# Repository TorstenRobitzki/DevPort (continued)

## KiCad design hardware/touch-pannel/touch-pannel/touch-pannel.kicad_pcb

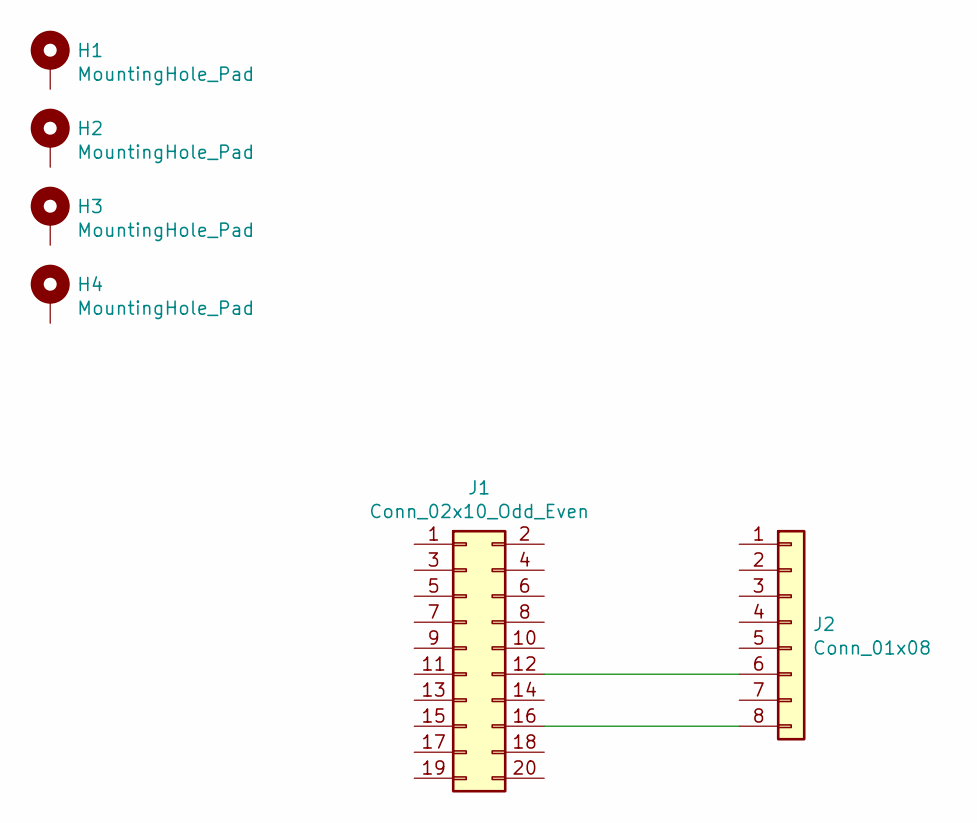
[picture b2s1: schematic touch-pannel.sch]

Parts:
H1, H2, H3, H4: MountingHole_Pad; MountingHole_3.2mm_M3_Pad_Via
J1: Conn_02x10_Odd_Even; Molex_SlimStack_52991-0208_2x10_P0.50mm_Vertical
J2: Conn_01x08; wheel

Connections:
unnamed: H1.1, H1.~
unnamed: J1.2, J2.1
unnamed: J1.4, J2.2
unnamed: J1.6, J2.3
unnamed: J1.8, J2.4
unnamed: J1.10, J2.5
unnamed: J1.12, J2.6
unnamed: J1.14, J2.7
unnamed: J1.16, J2.8

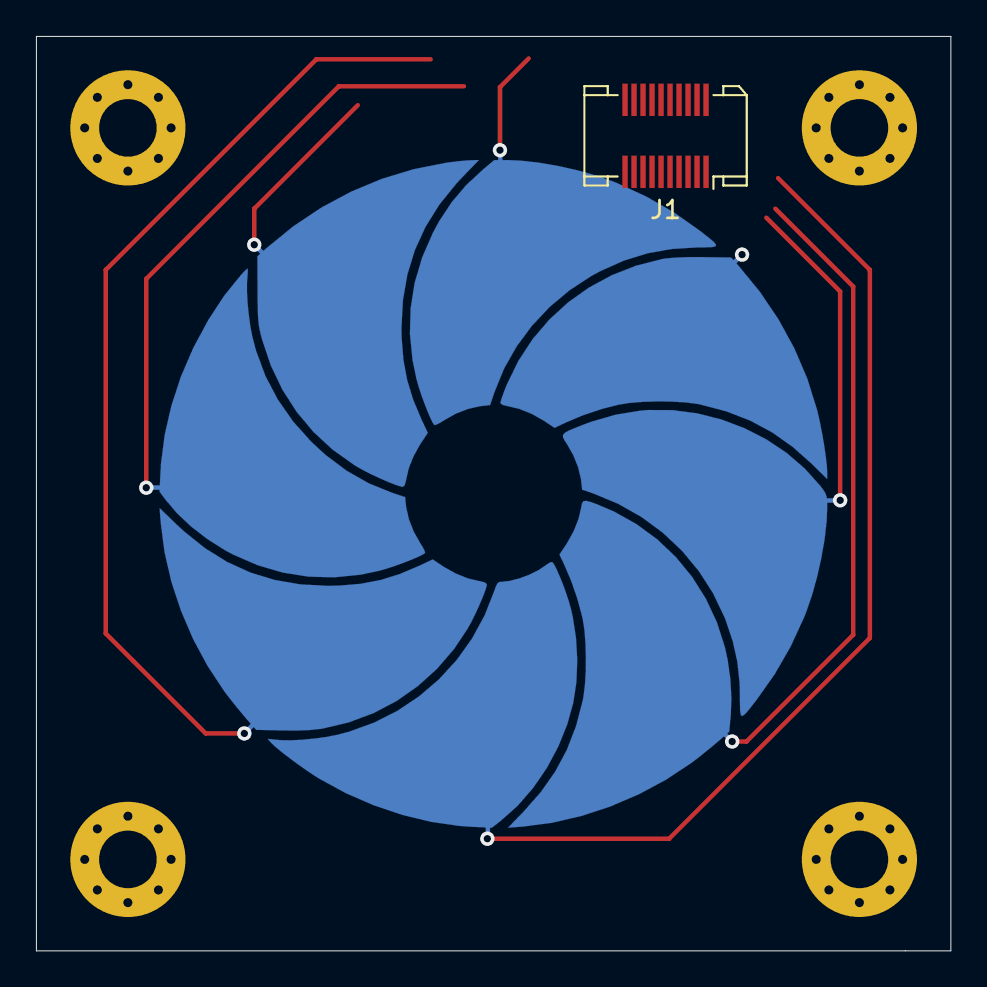
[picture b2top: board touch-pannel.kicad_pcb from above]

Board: 2 copper layers, 50.8 x 50.8 mm, 6 parts (1 on the bottom side), 9 nets.

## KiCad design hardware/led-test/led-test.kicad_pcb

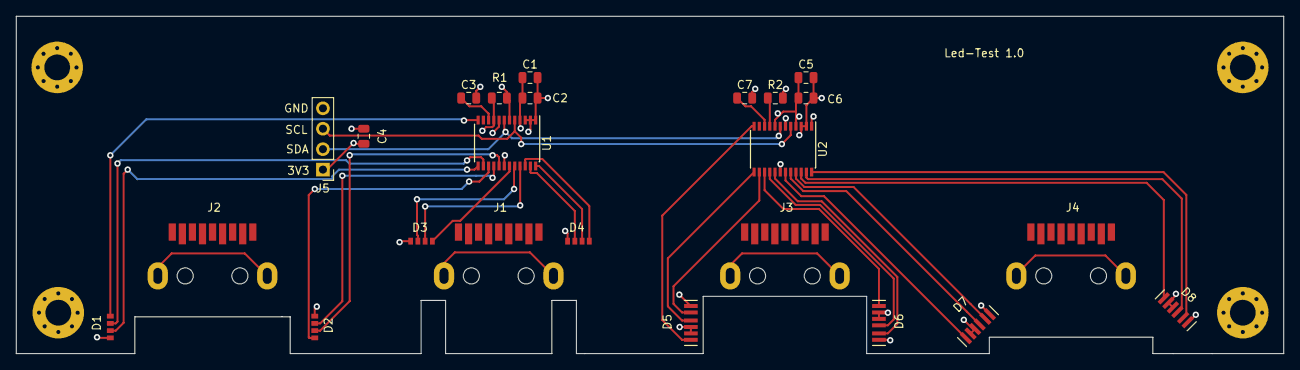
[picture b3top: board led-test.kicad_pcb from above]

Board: 4 copper layers, 157.5 x 41.9 mm, 24 parts (0 on the bottom side), 32 nets.

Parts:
C1, C3, C5, C7: 1µF; C_0805_2012Metric
C2, C6: 0.1µF; C_0805_2012Metric
C4: 10µF; C_0805_2012Metric
D1, D2, D3, D4: LED_AGBR; MSL0601RGB
D5, D6, D7, D8: LED_RGB; KRTB_AELPS1.32
J1, J2, J3, J4: USB3_A; WR-COM_USB_3.0_Horizontal_SMT
J5: Conn_01x04_Male; PinHeader_1x04_P2.54mm_Vertical
R1, R2: 3.6k; R_0805_2012Metric
U1, U2: LP5012PWR; TSSOP-24_4.4x7.8mm_P0.65mm

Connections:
+3V3: C1.1, C2.1, C4.1, C5.1, C6.1, D1.1, D2.1, D3.1, D4.1, D5.4, D5.5, D5.6, D6.4, D6.5, D6.6, D7.4, D7.5, D7.6, D8.4, D8.5, D8.6, J5.1, U1.4, U1.8, U2.1, U2.4, U2.8
/SCL: J5.3, U1.5, U2.5
/SDA: J5.2, U1.7, U2.7
GND: C1.2, C2.2, C3.2, C4.2, C5.2, C6.2, C7.2, J5.4, R1.2, R2.2, U1.1, U1.2, U1.3, U1.6, U1.18, U2.2, U2.3, U2.6, U2.18
unnamed: C3.1, U1.10
unnamed: C7.1, U2.10
unnamed: D1.2, U1.13
unnamed: D1.3, U1.14
unnamed: D1.4, U1.12
unnamed: D2.2, U1.16
unnamed: D2.3, U1.17
unnamed: D2.4, U1.15
unnamed: D3.2, U1.20
unnamed: D3.3, U1.21
unnamed: D3.4, U1.19
unnamed: D4.2, U1.23
unnamed: D4.3, U1.24
unnamed: D4.4, U1.22
unnamed: D5.1, U2.12
unnamed: D5.2, U2.13
unnamed: D5.3, U2.14
unnamed: D6.1, U2.15
unnamed: D6.2, U2.16
unnamed: D6.3, U2.17
unnamed: D7.1, U2.19
unnamed: D7.2, U2.20
unnamed: D7.3, U2.21
unnamed: D8.1, U2.22
unnamed: D8.2, U2.23
unnamed: D8.3, U2.24
unnamed: R1.1, U1.9
unnamed: R2.1, U2.9

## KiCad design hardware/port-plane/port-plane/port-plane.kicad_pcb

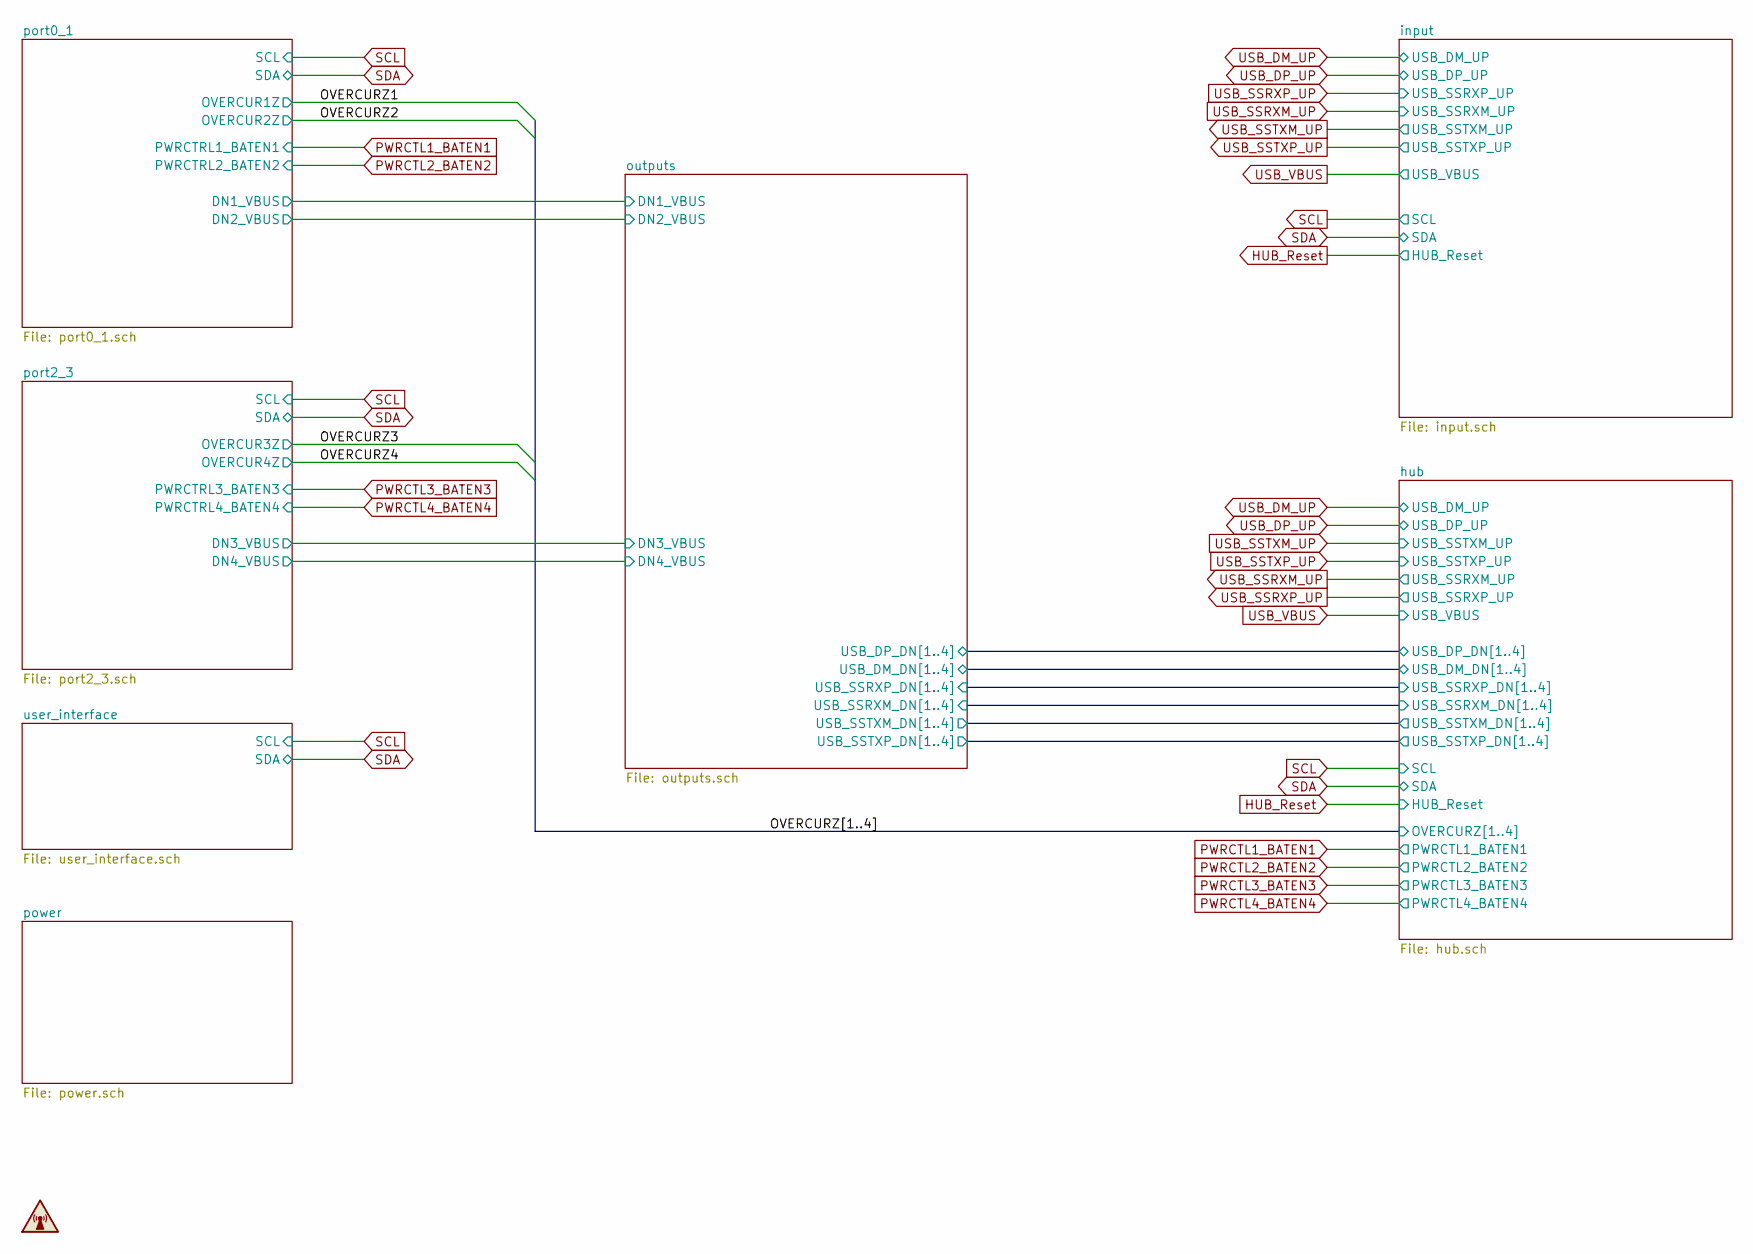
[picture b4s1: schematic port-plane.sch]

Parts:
SYM1: SYM_Radio_Waves_Small; Torrox_Black

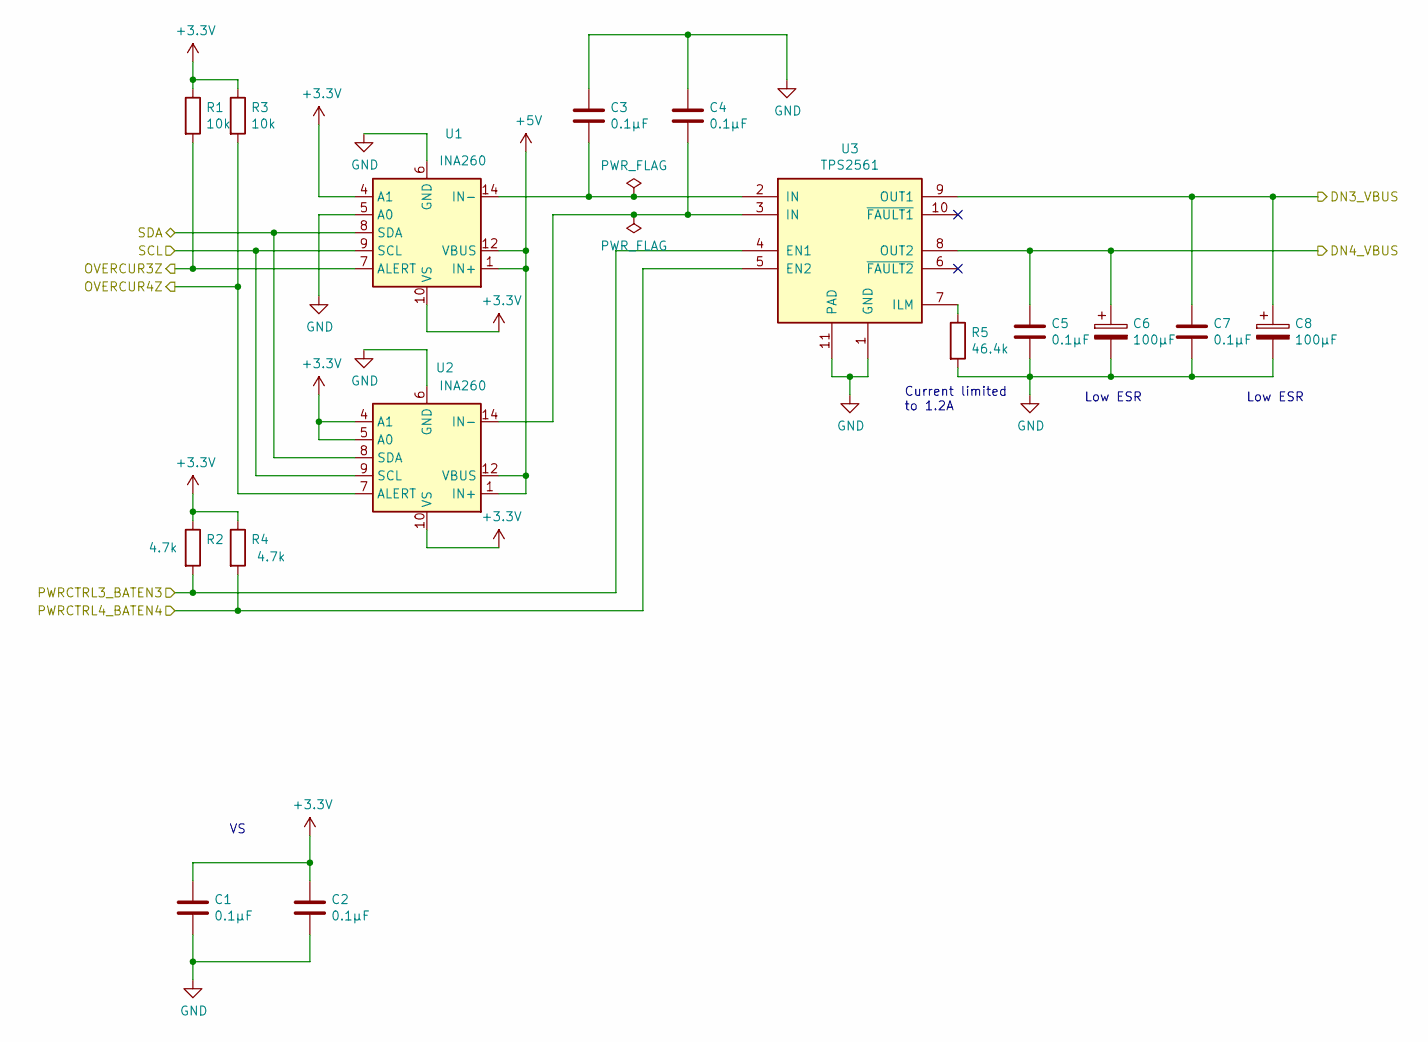
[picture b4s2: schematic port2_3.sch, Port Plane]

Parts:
C1, C2, C3, C4, C5, C7: 0.1µF; C_0603_1608Metric
C6, C8: 100µF; C_Elec_6.3x7.7
R1, R3: 10k; R_0603_1608Metric
R2, R4: 4.7k; R_0603_1608Metric
R5: 46.4k; R_0603_1608Metric
U1, U2: INA260; TSSOP-16_4.4x5mm_P0.65mm
U3: TPS2561; VSON-10-1EP_3x3mm_P0.5mm_EP1.65x2.4mm_ThermalVias

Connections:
+5V: U1.1 (IN+), U1.2 (IN+), U1.3 (IN+), U1.12 (VBUS), U2.1 (IN+), U2.2 (IN+), U2.3 (IN+), U2.12 (VBUS); also elsewhere on the board
/OVERCURZ3: R1.2, U1.7 (ALERT); also elsewhere on the board
/OVERCURZ4: R3.2, U2.7 (ALERT); also elsewhere on the board
/outputs/DN3_VBUS: C7.1, C8.1, U3.9 (OUT1); also elsewhere on the board
/outputs/DN4_VBUS: C5.1, C6.1, U3.8 (OUT2); also elsewhere on the board
GND: C1.2, C2.2, C3.1, C4.1, C5.2, C6.2, C7.2, C8.2, R5.2, U1.5 (A0), U1.6 (GND), U1.11 (GND), U2.6 (GND), U2.11 (GND), U3.1 (GND), U3.11 (PAD); also elsewhere on the board
unnamed: C3.2, U1.14 (IN-), U1.15 (IN-), U1.16 (IN-), U3.2 (IN)
unnamed: C4.2, U2.14 (IN-), U2.15 (IN-), U2.16 (IN-), U3.3 (IN)
unnamed: R5.1, U3.7 (ILM)
PWRCTL3_BATEN3: R2.2, U3.4 (EN1); also elsewhere on the board
PWRCTL4_BATEN4: R4.2, U3.5 (EN2); also elsewhere on the board

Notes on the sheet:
Current limited to 1.2A
Low ESR

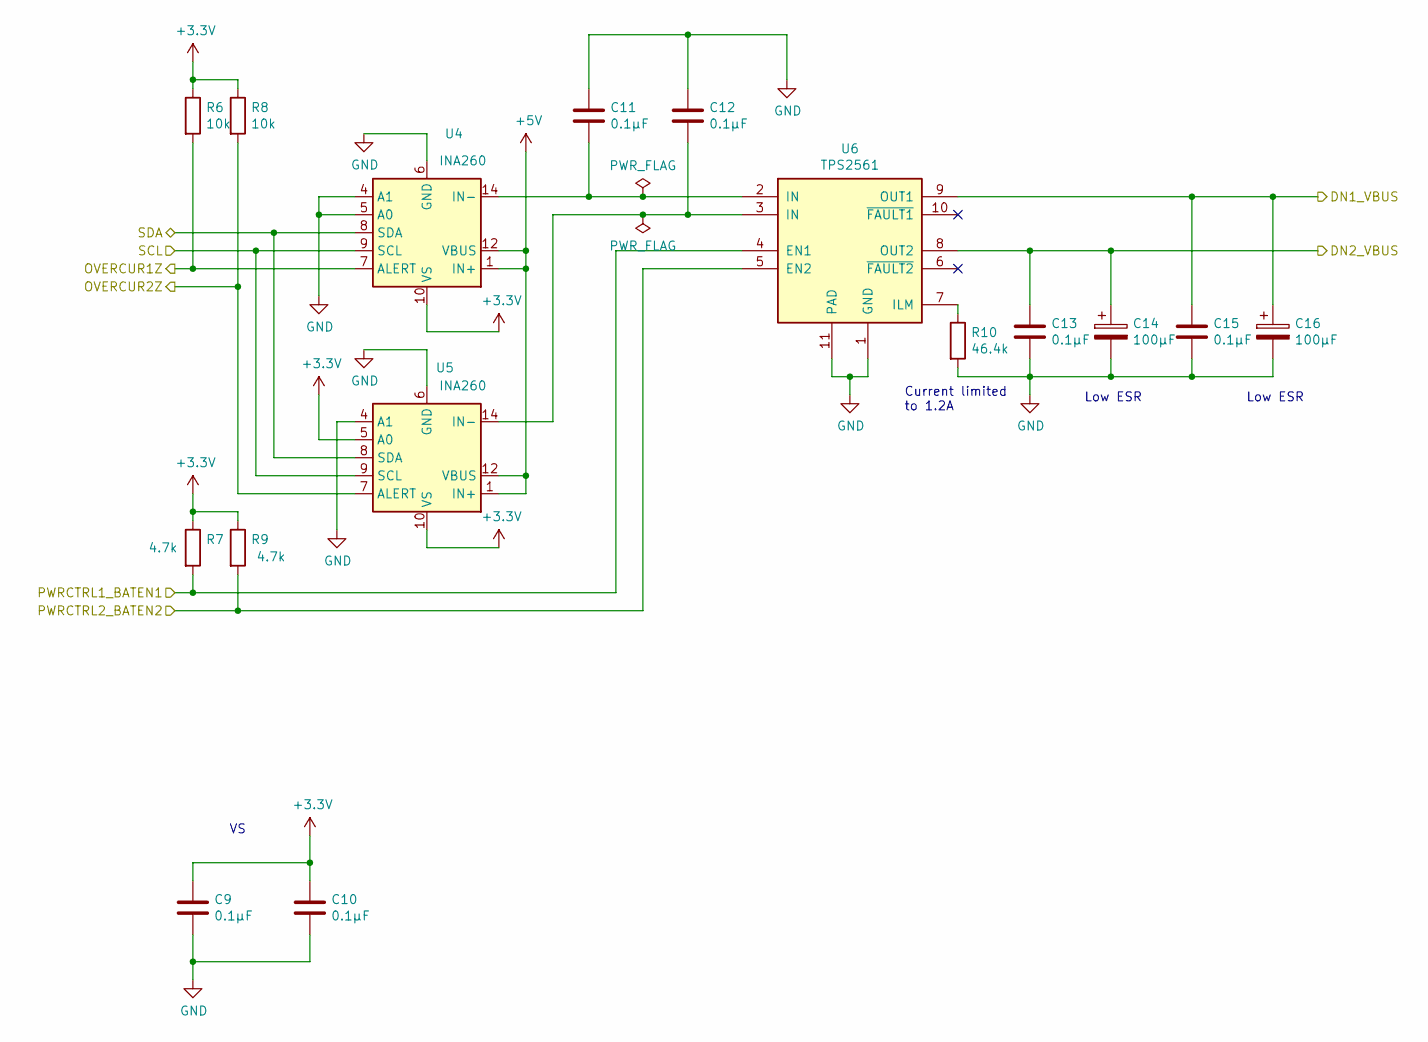
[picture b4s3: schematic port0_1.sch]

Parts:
C9, C10, C11, C12, C13, C15: 0.1µF; C_0603_1608Metric
C14, C16: 100µF; C_Elec_6.3x7.7
R6, R8: 10k; R_0603_1608Metric
R7, R9: 4.7k; R_0603_1608Metric
R10: 46.4k; R_0603_1608Metric
U4, U5: INA260; TSSOP-16_4.4x5mm_P0.65mm
U6: TPS2561; VSON-10-1EP_3x3mm_P0.5mm_EP1.65x2.4mm_ThermalVias

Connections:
+5V: U4.1 (IN+), U4.2 (IN+), U4.3 (IN+), U4.12 (VBUS), U5.1 (IN+), U5.2 (IN+), U5.3 (IN+), U5.12 (VBUS); also elsewhere on the board
/OVERCURZ1: R6.2, U4.7 (ALERT); also elsewhere on the board
/OVERCURZ2: R8.2, U5.7 (ALERT); also elsewhere on the board
/outputs/DN1_VBUS: C15.1, C16.1, U6.9 (OUT1); also elsewhere on the board
/outputs/DN2_VBUS: C13.1, C14.1, U6.8 (OUT2); also elsewhere on the board
GND: C9.2, C10.2, C11.1, C12.1, C13.2, C14.2, C15.2, C16.2, R10.2, U4.4 (A1), U4.5 (A0), U4.6 (GND), U4.11 (GND), U5.4 (A1), U5.6 (GND), U5.11 (GND), U6.1 (GND), U6.11 (PAD); also elsewhere on the board
unnamed: C11.2, U4.14 (IN-), U4.15 (IN-), U4.16 (IN-), U6.2 (IN)
unnamed: C12.2, U5.14 (IN-), U5.15 (IN-), U5.16 (IN-), U6.3 (IN)
unnamed: R10.1, U6.7 (ILM)
PWRCTL1_BATEN1: R7.2, U6.4 (EN1); also elsewhere on the board
PWRCTL2_BATEN2: R9.2, U6.5 (EN2); also elsewhere on the board

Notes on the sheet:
Current limited to 1.2A
Low ESR

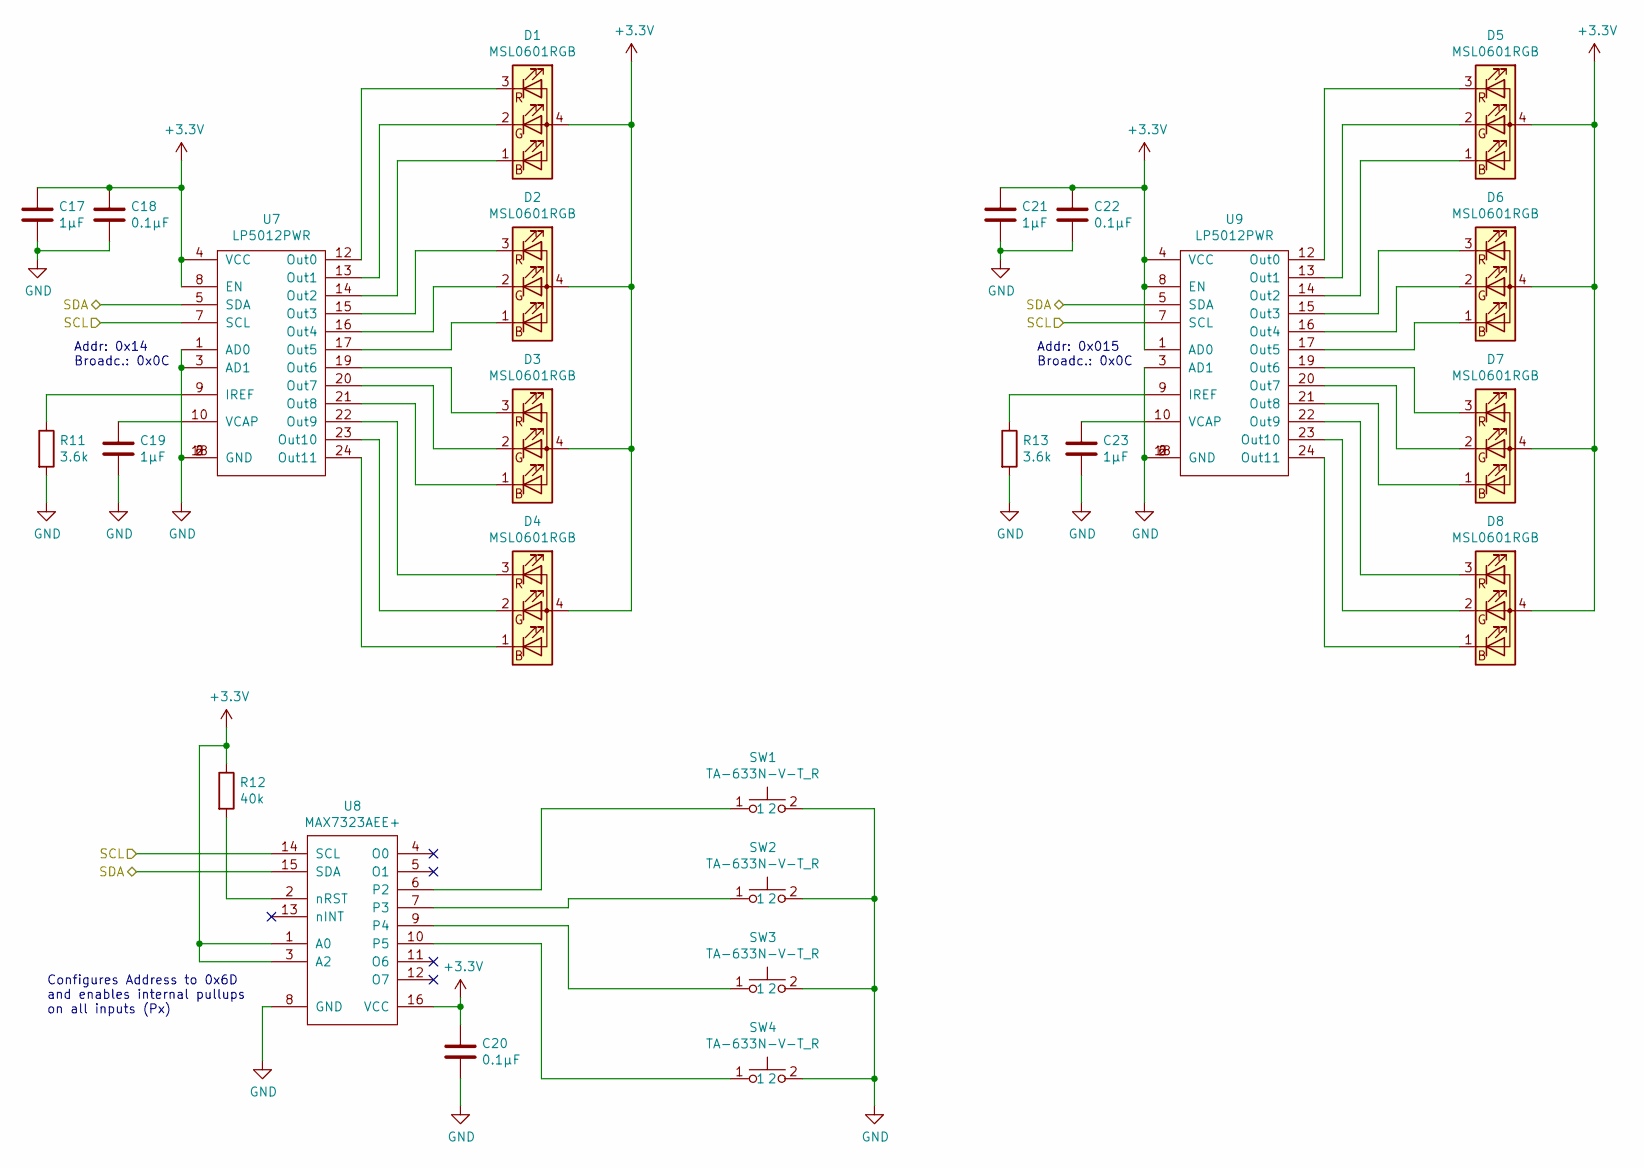
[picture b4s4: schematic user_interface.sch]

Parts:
C17, C19, C21, C23: 1µF; C_0603_1608Metric
C18, C20, C22: 0.1µF; C_0603_1608Metric
D1, D2, D3, D4, D5, D6, D7, D8: MSL0601RGB
R11, R13: 3.6k; R_0603_1608Metric
R12: 40k; R_0603_1608Metric
SW1, SW2, SW3, SW4: TA-633N-V-T_R; TA-633
U7, U9: LP5012PWR; TSSOP-24_4.4x7.8mm_P0.65mm
U8: MAX7323AEE+; TSSOP-24_4.4x7.8mm_P0.65mm

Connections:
GND: C17.2, C18.2, C19.2, C20.2, C21.2, C22.2, C23.2, R11.2, R13.2, SW1.2, SW2.2, SW3.2, SW4.2, U7.1 (AD0), U7.2 (GND), U7.3 (AD1), U7.6 (GND), U7.18 (GND), U8.8 (GND), U9.2 (GND), U9.3 (AD1), U9.6 (GND), U9.18 (GND); also elsewhere on the board
unnamed: C19.1, U7.10 (VCAP)
unnamed: C23.1, U9.10 (VCAP)
unnamed: D1.1 (BK), U7.14 (Out2)
unnamed: D1.2 (GK), U7.13 (Out1)
unnamed: D1.3 (RK), U7.12 (Out0)
unnamed: D2.1 (BK), U7.17 (Out5)
unnamed: D2.2 (GK), U7.16 (Out4)
unnamed: D2.3 (RK), U7.15 (Out3)
unnamed: D3.1 (BK), U7.21 (Out8)
unnamed: D3.2 (GK), U7.20 (Out7)
unnamed: D3.3 (RK), U7.19 (Out6)
unnamed: D4.1 (BK), U7.24 (Out11)
unnamed: D4.2 (GK), U7.23 (Out10)
unnamed: D4.3 (RK), U7.22 (Out9)
unnamed: D5.1 (BK), U9.14 (Out2)
unnamed: D5.2 (GK), U9.13 (Out1)
unnamed: D5.3 (RK), U9.12 (Out0)
unnamed: D6.1 (BK), U9.17 (Out5)
unnamed: D6.2 (GK), U9.16 (Out4)
unnamed: D6.3 (RK), U9.15 (Out3)
unnamed: D7.1 (BK), U9.21 (Out8)
unnamed: D7.2 (GK), U9.20 (Out7)
unnamed: D7.3 (RK), U9.19 (Out6)
unnamed: D8.1 (BK), U9.24 (Out11)
unnamed: D8.2 (GK), U9.23 (Out10)
unnamed: D8.3 (RK), U9.22 (Out9)
unnamed: R11.1, U7.9 (IREF)
unnamed: R12.2, U8.2 (nRST)
unnamed: R13.1, U9.9 (IREF)
unnamed: SW1.1, U8.6 (P2)
unnamed: SW2.1, U8.7 (P3)
unnamed: SW3.1, U8.9 (P4)
unnamed: SW4.1, U8.10 (P5)

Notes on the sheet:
Configures Address to 0x6D and enables internal pullups on all inputs (Px)
Addr: 0x14 Broadc.: 0x0C
Addr: 0x015 Broadc.: 0x0C

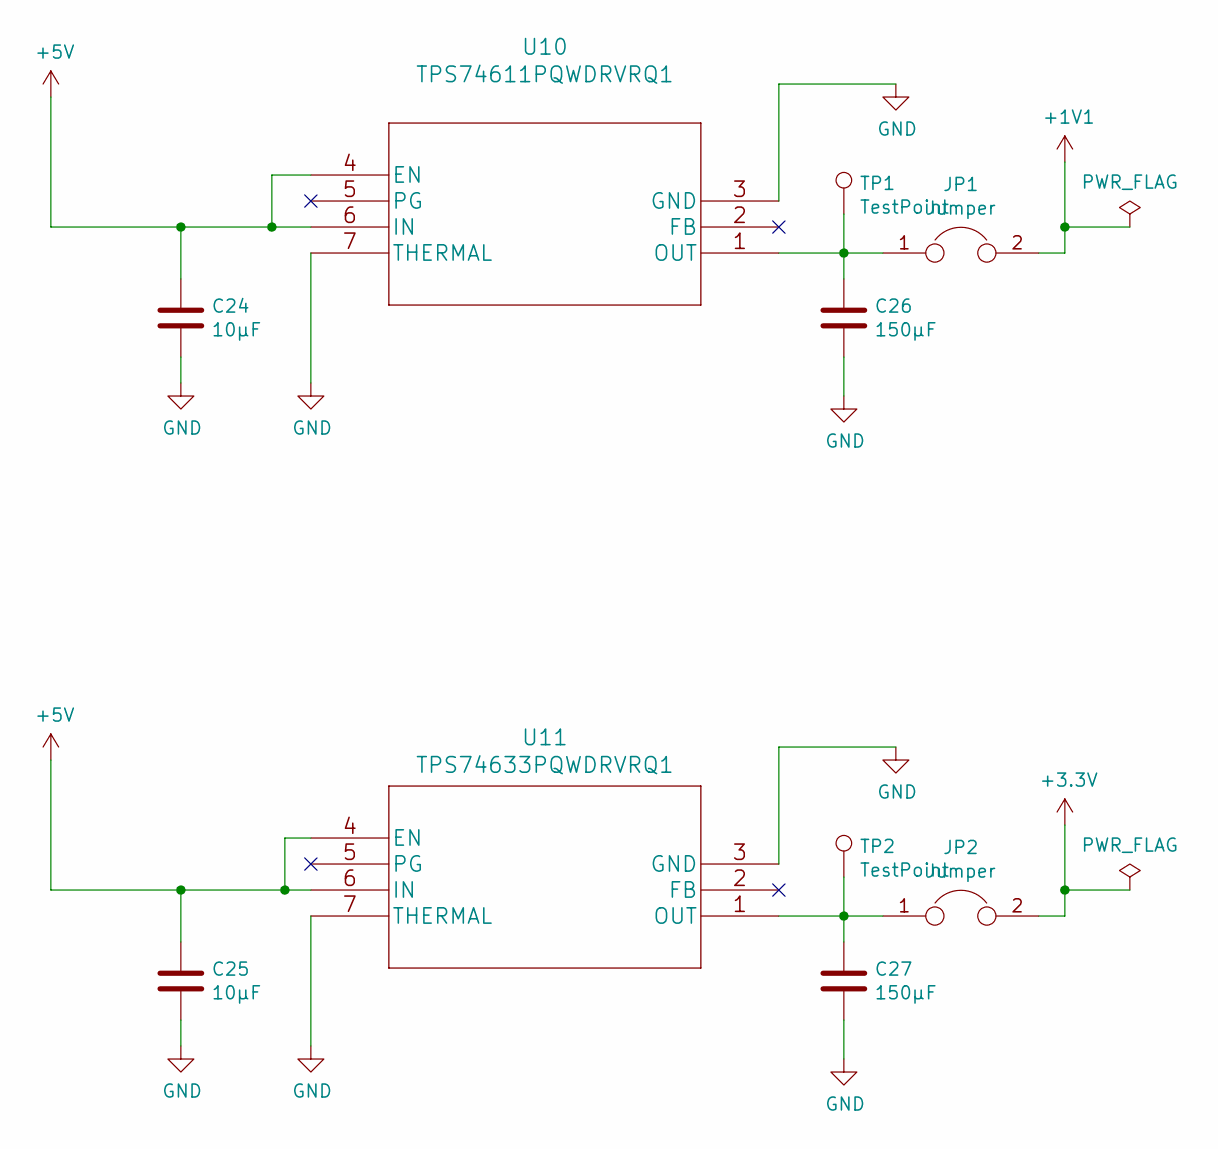
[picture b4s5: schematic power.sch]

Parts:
C24, C25: 10µF; C_0603_1608Metric
C26, C27: 150µF; C_1210_3225Metric
JP1, JP2: Jumper; SolderJumper-2_P1.3mm_Bridged_RoundedPad1.0x1.5mm
TP1, TP2: TestPoint; TestPoint_THTPad_1.0x1.0mm_Drill0.5mm
U10: TPS74611PQWDRVRQ1; TPS74601PBQWDRVRQ1
U11: TPS74633PQWDRVRQ1; TPS74601PBQWDRVRQ1

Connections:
+1V1: JP1.2; also elsewhere on the board
+5V: C24.1, C25.1, U10.4 (EN), U10.6 (IN), U11.4 (EN), U11.6 (IN); also elsewhere on the board
GND: C24.2, C25.2, C26.2, C27.2, U10.3 (GND), U10.7 (THERMAL), U11.3 (GND), U11.7 (THERMAL); also elsewhere on the board
unnamed: C26.1, JP1.1, TP1.1, U10.1 (OUT)
unnamed: C27.1, JP2.1, TP2.1, U11.1 (OUT)

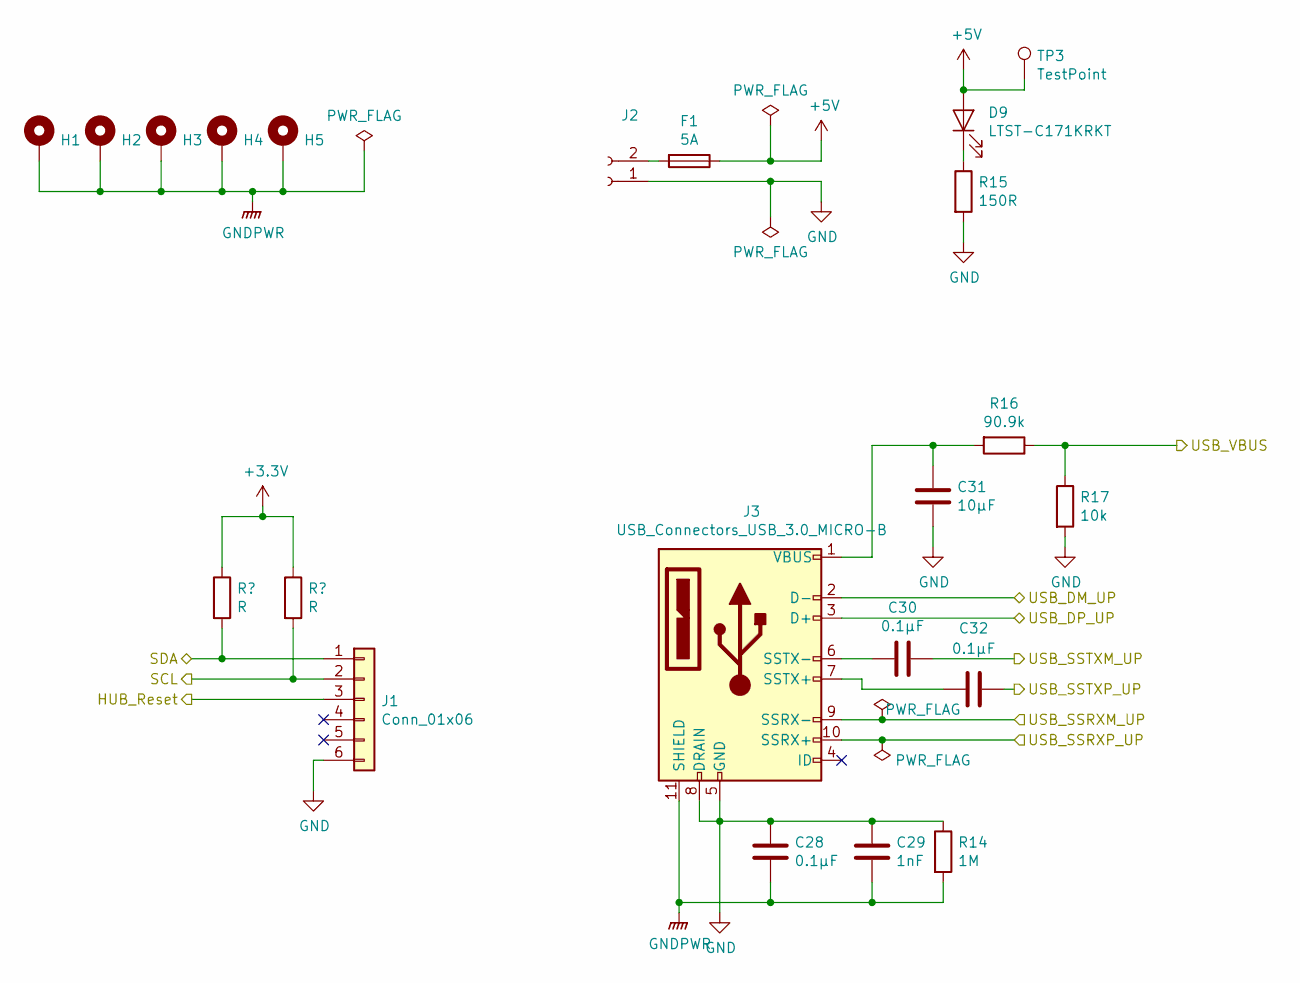
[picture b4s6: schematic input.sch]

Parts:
C28, C30, C32: 0.1µF; C_0603_1608Metric
C29: 1nF; C_0603_1608Metric
C31: 10µF; C_0603_1608Metric
D9: LTST-C171KRKT; LED_0805_2012Metric
F1: 5A; Fuse_0603_1608Metric_Pad1.05x0.95mm_HandSolder
H1, H2, H3, H4, H5: MountingHole_Pad; MountingHole_3.2mm_M3_Pad_Via
J1: Conn_01x06; PinHeader_2x03_P1.27mm_Vertical_SMD
J2: Conn_01x02_Female; Molex_Mini-Fit_Jr_5566-02A_2x01_P4.20mm_Vertical
J3: USB_Connectors_USB_3.0_MICRO-B; 692622420101
R14: 1M; R_0603_1608Metric
R15: 150R; R_0603_1608Metric
R16: 90.9k; R_0603_1608Metric
R17: 10k; R_0603_1608Metric
TP3: TestPoint; TestPoint_THTPad_1.0x1.0mm_Drill0.5mm

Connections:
+5V: D9.2 (A), F1.1, TP3.1; also elsewhere on the board
GND: C28.1, C29.1, C31.1, J1.6, J2.1, J3.5 (GND), J3.8 (DRAIN), R14.1, R15.2, R17.2; also elsewhere on the board
GNDPWR: C28.2, C29.2, H1.1, H2.1, H3.1, H4.1, H5.1, J3.11 (SHIELD), R14.2; also elsewhere on the board
HUB_Reset: J1.3; also elsewhere on the board
unnamed: C30.2, J3.6 (SSTX-)
unnamed: C31.2, J3.1 (VBUS), R16.2
unnamed: C32.2, J3.7 (SSTX+)
unnamed: D9.1 (K), R15.1
unnamed: F1.2, J2.2
USB_DM_UP: J3.2 (D-); also elsewhere on the board
USB_DP_UP: J3.3 (D+); also elsewhere on the board
USB_SSRXM_UP: J3.9 (SSRX-); also elsewhere on the board
USB_SSRXP_UP: J3.10 (SSRX+); also elsewhere on the board
USB_SSTXM_UP: C30.1; also elsewhere on the board
USB_SSTXP_UP: C32.1; also elsewhere on the board
USB_VBUS: R16.1, R17.1; also elsewhere on the board

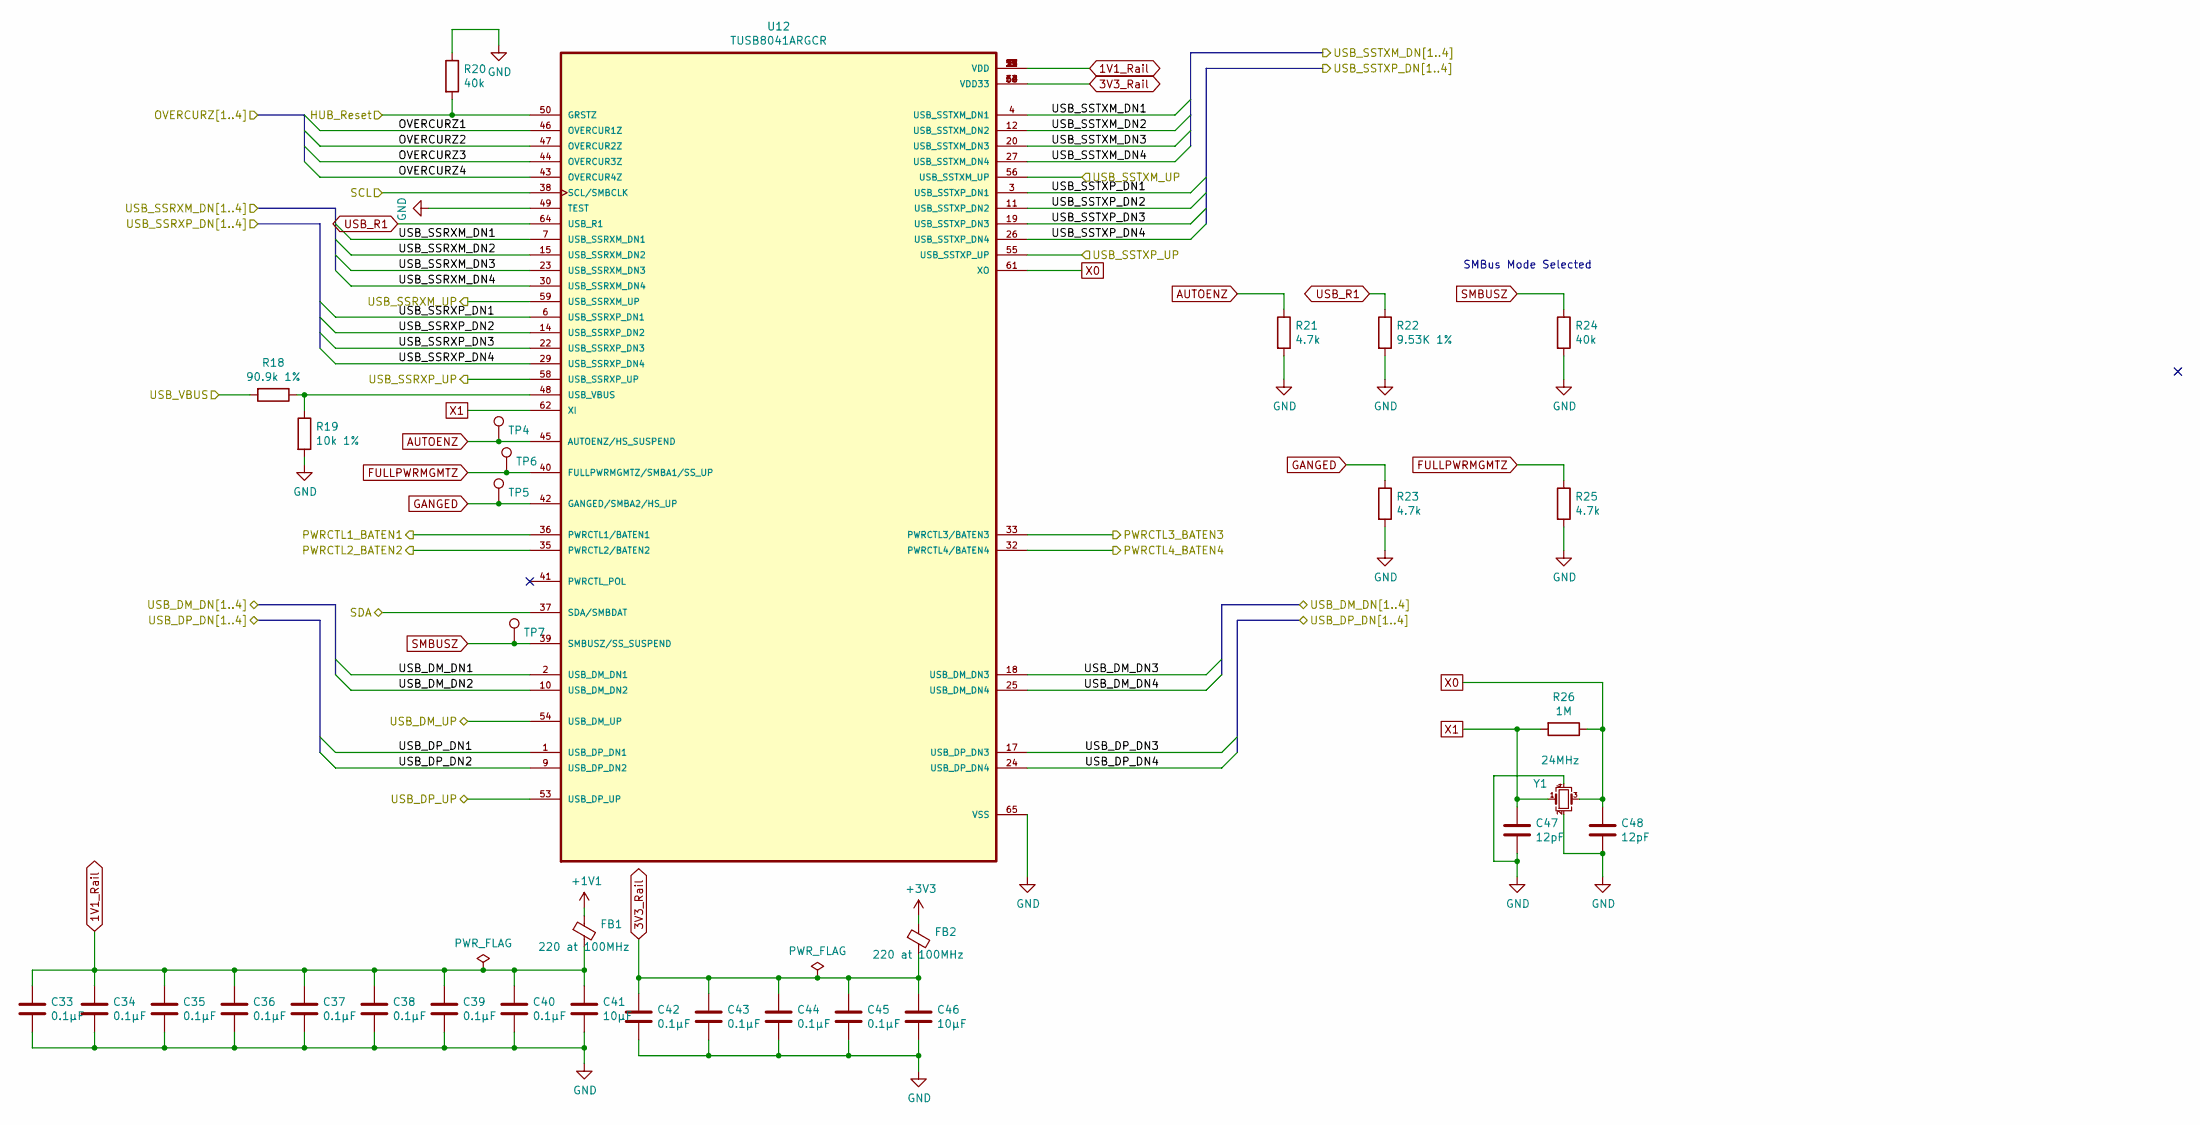
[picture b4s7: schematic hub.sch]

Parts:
C33, C34, C35, C36, C37, C38, C39, C40, C42, C43, C44, C45: 0.1µF; C_0603_1608Metric
C41, C46: 10µF; C_0603_1608Metric
C47, C48: 12pF; C_0603_1608Metric
FB1, FB2: 220 at 100MHz; L_0603_1608Metric
R18: 90.9k 1%; R_0603_1608Metric
R19: 10k 1%; R_0603_1608Metric
R20, R24: 40k; R_0603_1608Metric
R21, R23, R25: 4.7k; R_0603_1608Metric
R22: 9.53K 1%; R_0603_1608Metric
R26: 1M; R_0603_1608Metric
TP4, TP5, TP6, TP7: TestPoint; TestPoint_THTPad_1.0x1.0mm_Drill0.5mm
U12: TUSB8041ARGCR; QFN50P900X900X100-65N
Y1: 24MHz; Crystal_SMD_3225-4Pin_3.2x2.5mm

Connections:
1V1_Rail: C33.1, C34.1, C35.1, C36.1, C37.1, C38.1, C39.1, C40.1, C41.1, FB1.2, U12.5 (VDD), U12.8 (VDD), U12.13 (VDD), U12.21 (VDD), U12.28 (VDD), U12.31 (VDD), U12.51 (VDD), U12.57 (VDD)
3V3_Rail: C42.1, C43.1, C44.1, C45.1, C46.1, FB2.2, U12.16 (VDD33), U12.34 (VDD33), U12.52 (VDD33), U12.63 (VDD33)
+1V1: FB1.1; also elsewhere on the board
/OVERCURZ1: U12.46 (OVERCUR1Z); also elsewhere on the board
/OVERCURZ2: U12.47 (OVERCUR2Z); also elsewhere on the board
/OVERCURZ3: U12.44 (OVERCUR3Z); also elsewhere on the board
/OVERCURZ4: U12.43 (OVERCUR4Z); also elsewhere on the board
/hub/USB_DM_DN1: U12.2 (USB_DM_DN1); also elsewhere on the board
/hub/USB_DM_DN2: U12.10 (USB_DM_DN2); also elsewhere on the board
/hub/USB_DM_DN3: U12.18 (USB_DM_DN3); also elsewhere on the board
/hub/USB_DM_DN4: U12.25 (USB_DM_DN4); also elsewhere on the board
/hub/USB_DP_DN1: U12.1 (USB_DP_DN1); also elsewhere on the board
/hub/USB_DP_DN2: U12.9 (USB_DP_DN2); also elsewhere on the board
/hub/USB_DP_DN3: U12.17 (USB_DP_DN3); also elsewhere on the board
/hub/USB_DP_DN4: U12.24 (USB_DP_DN4); also elsewhere on the board
/hub/USB_SSRXM_DN1: U12.7 (USB_SSRXM_DN1); also elsewhere on the board
/hub/USB_SSRXM_DN2: U12.15 (USB_SSRXM_DN2); also elsewhere on the board
/hub/USB_SSRXM_DN3: U12.23 (USB_SSRXM_DN3); also elsewhere on the board
/hub/USB_SSRXM_DN4: U12.30 (USB_SSRXM_DN4); also elsewhere on the board
/hub/USB_SSRXP_DN1: U12.6 (USB_SSRXP_DN1); also elsewhere on the board
/hub/USB_SSRXP_DN2: U12.14 (USB_SSRXP_DN2); also elsewhere on the board
/hub/USB_SSRXP_DN3: U12.22 (USB_SSRXP_DN3); also elsewhere on the board
/hub/USB_SSRXP_DN4: U12.29 (USB_SSRXP_DN4); also elsewhere on the board
/hub/USB_SSTXM_DN1: U12.4 (USB_SSTXM_DN1); also elsewhere on the board
/hub/USB_SSTXM_DN2: U12.12 (USB_SSTXM_DN2); also elsewhere on the board
/hub/USB_SSTXM_DN3: U12.20 (USB_SSTXM_DN3); also elsewhere on the board
/hub/USB_SSTXM_DN4: U12.27 (USB_SSTXM_DN4); also elsewhere on the board
/hub/USB_SSTXP_DN1: U12.3 (USB_SSTXP_DN1); also elsewhere on the board
/hub/USB_SSTXP_DN2: U12.11 (USB_SSTXP_DN2); also elsewhere on the board
/hub/USB_SSTXP_DN3: U12.19 (USB_SSTXP_DN3); also elsewhere on the board
/hub/USB_SSTXP_DN4: U12.26 (USB_SSTXP_DN4); also elsewhere on the board
AUTOENZ: R21.1, TP4.1, U12.45 (AUTOENZ/HS_SUSPEND)
FULLPWRMGMTZ: R25.1, TP6.1, U12.40 (FULLPWRMGMTZ/SMBA1/SS_UP)
GANGED: R23.1, TP5.1, U12.42 (GANGED/SMBA2/HS_UP)
GND: C33.2, C34.2, C35.2, C36.2, C37.2, C38.2, C39.2, C40.2, C41.2, C42.2, C43.2, C44.2, C45.2, C46.2, C47.2, C48.2, R19.2, R20.1, R21.2, R22.2, R23.2, R24.2, R25.2, U12.49 (TEST), U12.65 (VSS), Y1.2, Y1.4; also elsewhere on the board
HUB_Reset: R20.2, U12.50 (GRSTZ); also elsewhere on the board
unnamed: R18.1, R19.1, U12.48 (USB_VBUS)
PWRCTL1_BATEN1: U12.36 (PWRCTL1/BATEN1); also elsewhere on the board
PWRCTL2_BATEN2: U12.35 (PWRCTL2/BATEN2); also elsewhere on the board
PWRCTL3_BATEN3: U12.33 (PWRCTL3/BATEN3); also elsewhere on the board
PWRCTL4_BATEN4: U12.32 (PWRCTL4/BATEN4); also elsewhere on the board
SMBUSZ: R24.1, TP7.1, U12.39 (SMBUSZ/SS_SUSPEND)
USB_DM_UP: U12.54 (USB_DM_UP); also elsewhere on the board
USB_DP_UP: U12.53 (USB_DP_UP); also elsewhere on the board
USB_R1: R22.1, U12.64 (USB_R1)
USB_SSRXM_UP: U12.59 (USB_SSRXM_UP); also elsewhere on the board
USB_SSRXP_UP: U12.58 (USB_SSRXP_UP); also elsewhere on the board
USB_SSTXM_UP: U12.56 (USB_SSTXM_UP); also elsewhere on the board
USB_SSTXP_UP: U12.55 (USB_SSTXP_UP); also elsewhere on the board
USB_VBUS: R18.2; also elsewhere on the board
X0: C48.1, R26.1, U12.61 (XO), Y1.3
X1: C47.1, R26.2, U12.62 (XI), Y1.1

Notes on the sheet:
SMBus Mode Selected
